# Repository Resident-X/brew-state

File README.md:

# `brew-state` — a model-based controller for a dual-thermoblock espresso machine

Replacing the factory control board in a Sunbeam EM7000 with a controller that actually models the machine: state estimation, a forward horizon, flow and pressure profiling, and a hardware safety chain with no firmware anywhere in it.

This repository is **public domain**. Take any of it.

## How this project is built

Requirements first, then code. The `specs/` graph is finished before firmware starts, and this repo is partly an argument that working in that order is faster rather than slower.

That means the graph is the substance here, and anything under `specs/` describes the machine as it is meant to be — not as it currently is.

## Where to start reading

**If you want to know what this machine is meant to do**, read the personas and journeys first. They are written to be read by a person, not parsed by a tool:

- `specs/personas/` — three stakeholders. The **operator** who makes coffee, the **builder** who designs and commissions it, and the **adopter** who found this published and owns a different machine.
- `specs/journeys/` — what actually happens: pulling a shot, steaming a jug, serving a group, commissioning the plant, correcting drift, keeping the machine in condition.

**If you want to know what constrains it**, read `specs/obligations/`. These are the cross-cutting commitments — electrical and thermal safety, real-time discipline, control-design discipline, verification discipline, open-source maintainability, physical configuration control. The safety obligation is the only one whose authority is external to this project, and it outranks everything else in the graph.

**If you want the detail**, `specs/requirements/` holds the functional and constraint requirements, `specs/definitions/` the vocabulary, and `specs/decisions/` the choices that have been made and why — including the options that were rejected.

**If you are rebuilding this on your own machine**, read [`docs/sunbeam-em7000/reference-machine.md`](docs/sunbeam-em7000/reference-machine.md) first. Everything specific to *our* machine — supply voltage, mains frequency, element ratings, protection trip points — lives in that one file. The requirement graph is written without those values so that replacing that file is the whole job.

## Two different promises

Be clear about which of these you are:

- **Same architecture** (a dual-thermoblock machine): the graph should apply to you, and adapting it should mean supplying your own parameters rather than changing requirements.
- **Different architecture** (single boiler, heat exchanger): the requirements will not all fit — an HX group's temperature depends on time since the last shot, which has no representation in a thermoblock's state at any parameter values. What transfers is the **method**, the tooling and the safety architecture. That is a smaller promise, and it is the honest one.

## Reading the graph

Nodes are `.req.yaml` files — plain YAML with prose in them. Reading needs nothing but a text editor. **Changing them is a different matter, and is covered below.**

**How they connect.** A requirement `derives-from` one or more *criteria* of the node above it, so the chain runs persona → journey → requirement, with each node carrying numbered criteria (`REQ-BREW-TEMP-001.C1`) attached by `criterion-of`. Obligations sit across the top: they are not part of that chain but constrain everything under them, and the safety obligation outranks the lot. Requirements also derive from each other's criteria where one genuinely builds on another. Decisions attach by `addresses`.

**Priorities.** Every requirement carries one:

| | |
|---|---|
| `must` | the system is wrong without it |
| `should` | real value, deliberately ranked below the musts |
| `could` | worth having, and shipping without it is not a defect |

Priority is about whether the system is wrong, not about when something gets built.

## Changing the graph

**Do not hand-edit `.req.yaml` files.** The graph is maintained by [Staircase](#staircase), and the engine is what holds it together: it assigns IDs, places files, wires and validates links, enforces the boundary between the requirement and delivery chains, applies the authoring discipline, and records who changed what and when.

Editing a node by hand bypasses all of that, and the failure mode is quiet. The file still parses. What breaks is underneath — a link pointing at something that no longer exists, a criterion orphaned from its parent, a requirement deriving from a retired one, a change landing with no version behind it and no event recording it. Structural validation does not catch most of that, because nothing is malformed. It is simply wrong, and it stays wrong until something downstream fails for reasons that no longer look connected.

That is the whole reason the engine exists. It is not a formatter over some YAML — it is the thing that knows how a systems and delivery graph has to hold together, so that a person changing one node does not have to.

**A caveat you should know before relying on this.** The engine is not part of this repository and is not currently something you can obtain. So you can read everything here, and you can build from it, but you cannot presently maintain a fork of the graph the way it is meant to be maintained. That is a real limit on what this repo currently offers, and it is tracked in the graph itself rather than hidden — `REQ-PUBLISHED-BUILD-PATH-001` requires every tool the path depends on to be obtainable by someone who is not the author, and that criterion is not met today.

## Staircase

This project is built with Staircase, whose thesis is that disciplined, requirement-driven, complete-the-first-time engineering produces better software, faster, that stays maintainable. This repo is partly a test of that claim in public, on a real physical thing that can burn someone.

One discipline is worth knowing about while reading: **requirements state properties, not mechanisms.** You will not find part numbers, sensor technologies, interface choices or tuning constants in `specs/`. Those are decisions and they live separately. That is also what makes the graph portable to a machine on a different continent running on a different voltage — a requirement that names a mechanism does not travel.

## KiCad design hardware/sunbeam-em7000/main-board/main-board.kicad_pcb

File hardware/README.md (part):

# Hardware

Board designs and the check every one of them has to pass before it is ordered.

- `hardware/<machine>/` holds one machine's board designs, one KiCad project per board in its own folder, and the `separation-basis.yaml`, `pin-allocation.yaml`, `controller-part.yaml`, `parts-specification.yaml`, `catalogue-extract.yaml` and `board-rules.yaml` they are held to, and the `derating-policy.yaml` and `pin-limits.yaml` they are held to where a design's folders hold them.
- `hardware/tools/` holds the pre-order check, the locked-copper check used around routing, the command that renders a board's layout review views, the command that renders a placed board's placement view and measures it, the command that seeds the layout review's proof design, the review kit (the command that runs a declared judged review as forks of one shared context), the layout review's caller for it, the command that writes a committed board's review folder, the critical-routing check's caller and the catalogue helpers it shares with the layout caller, the production-files check's caller and the command that writes a real order's review folder, the schematic review's caller, the command that writes a committed schematic's review folder and the command that proves the fanned-out schematic review (with the proof harness it shares with the layout review's), the command that proves the fanned-out layout review, the commands that convert and draw a board's production files and the command that seeds the proof design's production files, and their tests. They work for any machine.
- `hardware/proof/` holds designs committed only to prove the board tooling and the layout review: `gate-proof` for the pre-order check's rules, `record-keys-proof` for the keys its records carry, `review-proof` for the layout review and the ordering step's production-files check, and `circuit-review-proof` for the schematic review. They are never ordered.

A **board design** is a KiCad project file (`.kicad_pro`) together with the schematic (`.kicad_sch`) and layout (`.kicad_pcb`) of the same name beside it. The check finds every design git tracks, wherever it sits. The layout above is a convention for readers, not something the check depends on. A design is checked once git tracks it: `git add` is enough for the design's own files. The check reads a design only as the repository holds it. KiCad is given a copy of the tracked files alone, each in its place in the repository: everything in the design's folder, every sheet its schematic reaches, and every library its `sym-lib-table` and `fp-lib-table` name, wherever in the repository they sit. A library, sheet or rules file left uncommitted is therefore not used. A sheet the schematic names, a custom rules file or library table beside the project, or a library a table names, that git does not track fails the design by name. So does a library the repository cannot hold at all: one named by an absolute path, one outside the repository, or one reached through a path variable other than `${KIPRJMOD}` and those naming the libraries KiCad installs with itself (`${KICAD10_SYMBOL_DIR}`, `${KICAD10_FOOTPRINT_DIR}` and the like). Name a library from its table as `${KIPRJMOD}/` followed by its path from the design's folder. The separation basis record has to be committed exactly as it stands (see below).

KiCad is run with a configuration the check makes for the run, not the one on the machine running it. That configuration names only the libraries KiCad installs with itself, and no `KICAD…` variable from the environment reaches KiCad. A symbol or footprint whose library only one machine's own KiCad setup names, in its global library tables or its path variables, is therefore reported by KiCad as a library its configuration does not include, and fails the design under `design_library`. Put such a library in the repository and name it in the design's own table.

One KiCad run may take at most 7200 s. The limit is the constant `KICAD_TIMEOUT_S` in `hardware/tools/board_check.py`, and `hardware/tools/board_views.py` reads the same constant, so neither tool has a figure of its own. A run that outlives it fails the design as "KiCad did not finish within 7200 s", with the limit in force named, in the check and in the views command; the wait is finite, so a hung run still fails. The figure rests on a measurement made on 2026-10-31 on the main board with its ground and neutral pours and slots: KiCad's creepage test alone took about 10 minutes and the full design check 20 to 30 minutes. 7200 s is about four times the slowest of those, the margin that lets a slower machine or a denser board finish.

## What you need

Every tool is free. The check stops with an error naming any tool that is missing or too old, rather than skipping the checks that need it.

| Tool | Minimum | Where to get it |
|---|---|---|
| KiCad (its `kicad-cli`) | KiCad 10.0 | https://www.kicad.org/download/. This repository's board files are in KiCad 10's format, which older versions cannot open. |
| Python | Python 3.9 | https://www.python.org/downloads/ |
| PyYAML | PyYAML 5.1 | `pip install pyyaml`, or your system's `python3-yaml` package |
| git | git 2.11 | https://git-scm.com/downloads |
| Task | 3 | https://taskfile.dev/installation/ |
| resvg, for the layout review views and for the tooling tests the build round runs | resvg 0.47 | A prebuilt program from https://github.com/linebender/resvg/releases: the v0.47.0 release carries one for each of Windows (`resvg-win64.zip`), macOS and Linux (x86_64), and later releases carry them for macOS and Linux only. Or `brew install resvg` with Homebrew, on macOS or Linux. Or `cargo install resvg` with a Rust toolchain from https://rustup.rs/, on any operating system. It turns the views into images. The pre-order check itself does not need it, but the tooling tests that the build round and the nightly run draw views, so those need it too ([When the board check runs](#when-the-board-check-runs)). |
| gerbonara, for the commands that draw a board's exported fabrication layers and for the tooling tests the build round runs | gerbonara 1.6.3, exactly | A Python library under the Apache licence, https://pypi.org/project/gerbonara/. Install it into a virtual environment of its own with `task hw:gerbonara`, which makes one in your user cache folder (`GERBONARA_VENV` puts it elsewhere), or by hand with `python3 -m venv <folder>` then `<folder>/bin/python -m pip install gerbonara==1.6.3` (on Windows `<folder>\Scripts\python.exe`) and name that environment's Python as `GERBONARA_PYTHON`. It reads the Gerber and drill files KiCad exports, which `kicad-cli` cannot, and the ordering step of the method turns each into a vector image that resvg rasterises. The pre-order check itself does not need it, but the tooling tests that the build round and the nightly run draw layers from exported files, so those need it too. A command or a test that needs it and does not find that version stops with `CANNOT RUN` naming it. |
| A monospaced font for the captions, for the layout review views and for the tooling tests the build round runs | DejaVu Sans Mono, or Menlo, Consolas, Liberation Mono or Courier New | The captions are drawn in the first of these that resvg finds among the system's fonts. macOS carries Menlo and Windows carries Consolas. Elsewhere, install DejaVu Sans Mono from https://dejavu-fonts.github.io/ or your system's package of it (for example `fonts-dejavu`). Without one the command, or the tooling tests, stop with `CANNOT RUN`. |

`kicad-cli` is often installed off the search path. The tasks use the variable `KICAD_CLI`, which defaults to the bare name `kicad-cli`. If it is not on your search path, set the variable to the tool's full path, either on the command line (`task hw:verify KICAD_CLI=/path/to/kicad-cli`) or in the environment. Its usual location:

| System | `kicad-cli` |
|---|---|
| macOS | `/Applications/KiCad/KiCad.app/Contents/MacOS/kicad-cli` |
| Windows | `C:\Program Files\KiCad\10.0\bin\kicad-cli.exe` |
| Linux (distribution or PPA package) | `/usr/bin/kicad-cli` |
| Linux (Flatpak) | not a file on the path: write a one-line script that runs `flatpak run --command=kicad-cli org.kicad.KiCad "$@"` and point `KICAD_CLI` at it |

`GERBONARA_PYTHON` is the Python of the virtual environment above. The tasks that draw layers use the variable, which defaults to the Python of the environment `task hw:gerbonara` makes and to `python3` when there is none, so only an environment made by hand needs it set, on the command line (`task hw:production-seed GERBONARA_PYTHON=/path/to/venv/bin/python -- ...`) or in the environment.

`resvg` is one program, wherever it was unpacked. The view tasks use the variable `RESVG`, which defaults to the bare name `resvg`. If it is not on your search path, set it to the program's full path, for example `task hw:views RESVG=/path/to/resvg -- ...`.

## The commands

- `task hw:verify` runs the pre-order check on every board design in the repository. It exits 0 only when every design passes. A build round runs it for a change that can matter to a board, and the nightly run of `main` runs it every night ([When the board check runs](#when-the-board-check-runs)).
- `task hw:prove` seeds each fault the check guards against into a throwaway copy of `hardware/proof/gate-proof` (or, for a fault about the keys of a record, of `hardware/proof/record-keys-proof`, for a fault about an unlisted pin of `hardware/proof/circuit-review-proof`, and for a fault about sensing clearance or ground returns of `hardware/proof/review-proof`) as the last commit holds it, in a temporary directory outside the repository, so an uncommitted edit to the proof design is not what it proves. It requires the check to catch each fault. This command is on demand: neither the build round nor the nightly runs it.
- `task hw:review-seed -- --seeds <file> --out <folder>` seeds known layout defects into a throwaway copy of `hardware/proof/review-proof` and writes a folder to review it blind, with the seed list apart (see [The proof designs](#the-proof-designs)). This command is on demand and is not part of the gate. It needs the same tools as `hw:views`.
- `task hw:production-review-folder -- --repo <repository> --commit <commit> --design <board folder> --out <folder> --work <folder> --views <folder> --placement <folder> --preview <folder> --preview-note <text> --tools <text> --command <text> ...` writes the review folder of a real order's production-files check for a judged review to read ([The production-files check by unit](#the-production-files-check-by-unit)). This command is on demand and is not part of the gate. It needs git and Python, no KiCad and no gerbonara.
- `task hw:production-seed -- --seeds <file> --out <folder>` seeds known defects into the production files of `hardware/proof/review-proof` and writes a folder to check them blind, with the seed list apart (see [The proof designs](#the-proof-designs)). This command is on demand and is not part of the gate. It needs the same tools as `hw:views`, and gerbonara.
- `task hw:test` runs the tests of the check itself, of the locked-copper check's four commands, of the layout review views, of the placement view, of the placement and critical routing history check, of the layout review record history check, of the layout review proof's seeding command, of the schematic sheet drawing command, of the review kit (its session specification and executors, answer reading, stream checks and telemetry, declaration, catalogue and shared context, planner and scheduler, merge and replicas, caller contract, contract smoke, the command and the task runner's file), of the layout review's caller, the critical-routing check's caller and the shared catalogue helpers, the production-files check's caller and its folder command, the schematic review's caller, the schematic review folder command and the schematic review proof command, the review folder command, the layout review proof command, the critical-routing review proof command and the production-files review proof command, and of the production-files conversion, rendering and seeding commands, against the real `kicad-cli`, `resvg` and gerbonara. It includes the tests that run the seeded-fault proof, so it is the whole suite, on demand.
- `task hw:test:round` runs the same tests without those that need the seeded-fault proof. It is the tooling-test part of the build round's board tier and of the nightly run ([When the board check runs](#when-the-board-check-runs)). It needs the same tools as `hw:test`: KiCad, resvg, a monospaced font and gerbonara.
  Both tasks run each test file in a process of its own, side by side, through `firmware/tools/run_tool_tests.py` (the runner the firmware tooling's tests use), from the repository root as a serial discovery run does. The runner fails when it finds no test file, names every file that fails, and writes a missing tool's `CANNOT RUN |` line once to its error output so the round reads it as a failure to look. The stage runs at most four files at once unless asked for more (`task hw:test -- --workers 10`), because the machine running the round is shared with other sessions; `task hw:test -- --workers 1` runs the files one after another. The long test files are divided by topic so no one file holds the stage: the KiCad check's tests into `test_board_check_kicad_*.py` (their shared setup and the exclusion of the seeded-fault proof in `board_kicad_fixtures.py`), the layout review views' into `test_board_views_*.py`, the history check's into `test_board_history_*.py`, the locked-copper check's into `test_locked_copper_*.py` and the review proof design's rules into `test_review_proof_rules_*.py`, each with its shared setup in a `*_fixtures.py` beside them; `test_board_kicad_division.py` holds each division to the tests the undivided file held, each in exactly one file. A test class whose tests only read a copy of a proof design and the result of checking it derives from `SharedCopy` and makes the copy and the check once, with the copy fingerprinted and verified unchanged after each test; a test that changes its copy derives from `Copy` and has one of its own.
- `task hw:reads` lists, one per line, every file the board designs git tracks read: each design's folder (with a trailing slash), its sheets, its libraries and the separation basis, pin allocation, controller part, parts specification, catalogue extract, derating policy, pin-limit, board rules and manufacturer limits records it is held to. It runs no check and needs only git and Python, no KiCad. The build round asks it which changed paths reach a board design.
- `task hw:review-run -- --caller <name> --review <folder> --out <folder>` runs a declared judged review as forks of one shared context ([The review kit command](#the-review-kit-command)). This command is on demand: neither the build round nor the nightly runs it. It needs the agent command line on the search path and logged in, and no KiCad.
- `task hw:review-smoke -- --out <folder>` runs the review kit's contract smoke, seven small probes of the installed agent command line for a few cents ([The review kit command](#the-review-kit-command)). This command is on demand: neither the build round nor the nightly runs it. It needs the agent command line on the search path and logged in, and no KiCad.
- `task hw:review-folder -- --repo <repository> --commit <commit> --design <board folder> --out <folder> ...` writes the review folder of a committed board for a judged review to read (with `--review critical-routing`, the critical-routing check's), and adds a rendered view or a text file to one it wrote ([The layout review by unit](#the-layout-review-by-unit), [The critical-routing check by unit](#the-critical-routing-check-by-unit)). This command is on demand and is not part of the gate. It needs git and Python and no KiCad.
- `task hw:review-proof -- --work <folder>` proves the fanned-out layout review on one seeded copy of `hardware/proof/review-proof` against the recorded single-reviewer runs, in one command ([The layout review by unit](#the-layout-review-by-unit)); with `--dry` it prints the plan and the predicted cost and time and starts no session. This command is on demand, spends the agent command line's usage and is not part of the gate. It needs the agent command line on the search path and logged in, and the same tools as `hw:review-seed`.
- `task hw:schematic-review-folder -- --repo <repository> --commit <commit> --design <board folder> --out <folder> --netlist <file> --netlist-command <text> --sheets <folder> --check-report <file> --number <n> --record <file> ...` writes the review folder of a committed schematic for the schematic review to read, and adds a sheet drawing, a view or a text file to one it wrote ([The schematic review by unit](#the-schematic-review-by-unit)). This command is on demand and is not part of the gate. It needs git and Python and no KiCad.
- `task hw:schematic-review-proof -- --work <folder> --seeded-repo <work tree> --seeds <file>` proves the fanned-out schematic review on one seeded copy of `hardware/proof/circuit-review-proof` against its single-reviewer run, in one command ([The schematic review by unit](#the-schematic-review-by-unit)); with `--dry` it prints the plan and the predicted cost and time and starts no session. This command is on demand, spends the agent command line's usage and is not part of the gate. It needs the agent command line on the search path and logged in, KiCad 10.0 or newer, and the seeding session's work tree and seed list.
- `task hw:critical-routing-review-proof -- --work <folder> --seeded-repo <work tree> --seeds <file>` proves the fanned-out critical-routing check on one seeded copy of `hardware/proof/method-proof` against its single-reviewer run, in one command ([The critical-routing check by unit](#the-critical-routing-check-by-unit)); with `--dry` it prints the plan and the predicted cost and time and starts no session. This command is on demand, spends the agent command line's usage and is not part of the gate. It needs the agent command line on the search path and logged in, the same tools as `hw:views`, and the seeding session's work tree and seed list.
- `task hw:production-files-review-proof -- --work <folder> --folder <production-files folder> --seeds <file>` proves the fanned-out production-files check on the seeded production files `task hw:production-seed` writes against its single-reviewer run, in one command ([The production-files check by unit](#the-production-files-check-by-unit)); with `--dry` it prints the plan and the predicted cost and time and starts no session. This command is on demand, spends the agent command line's usage and is not part of the gate. It needs the agent command line on the search path and logged in, and nothing else of its own: the folder and the seed list come from `hw:production-seed`.
- `task hw:views` renders every view the layout review judges one board on (below). It needs the same tools as `hw:verify`, and resvg.
- `task hw:placement` renders one placed board's placement view and writes its measures (below). It needs the same tools as `hw:views`.
- `task hw:sheets -- --out <folder>` draws every sheet of every board design git tracks, one image file for each sheet ([The schematic sheets](#the-schematic-sheets)). It needs KiCad and nothing else.
- `task hw:history` judges one board's placement and critical routing sections of its `layout-plan.md` against the repository's history (below). It needs git and Python only.
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
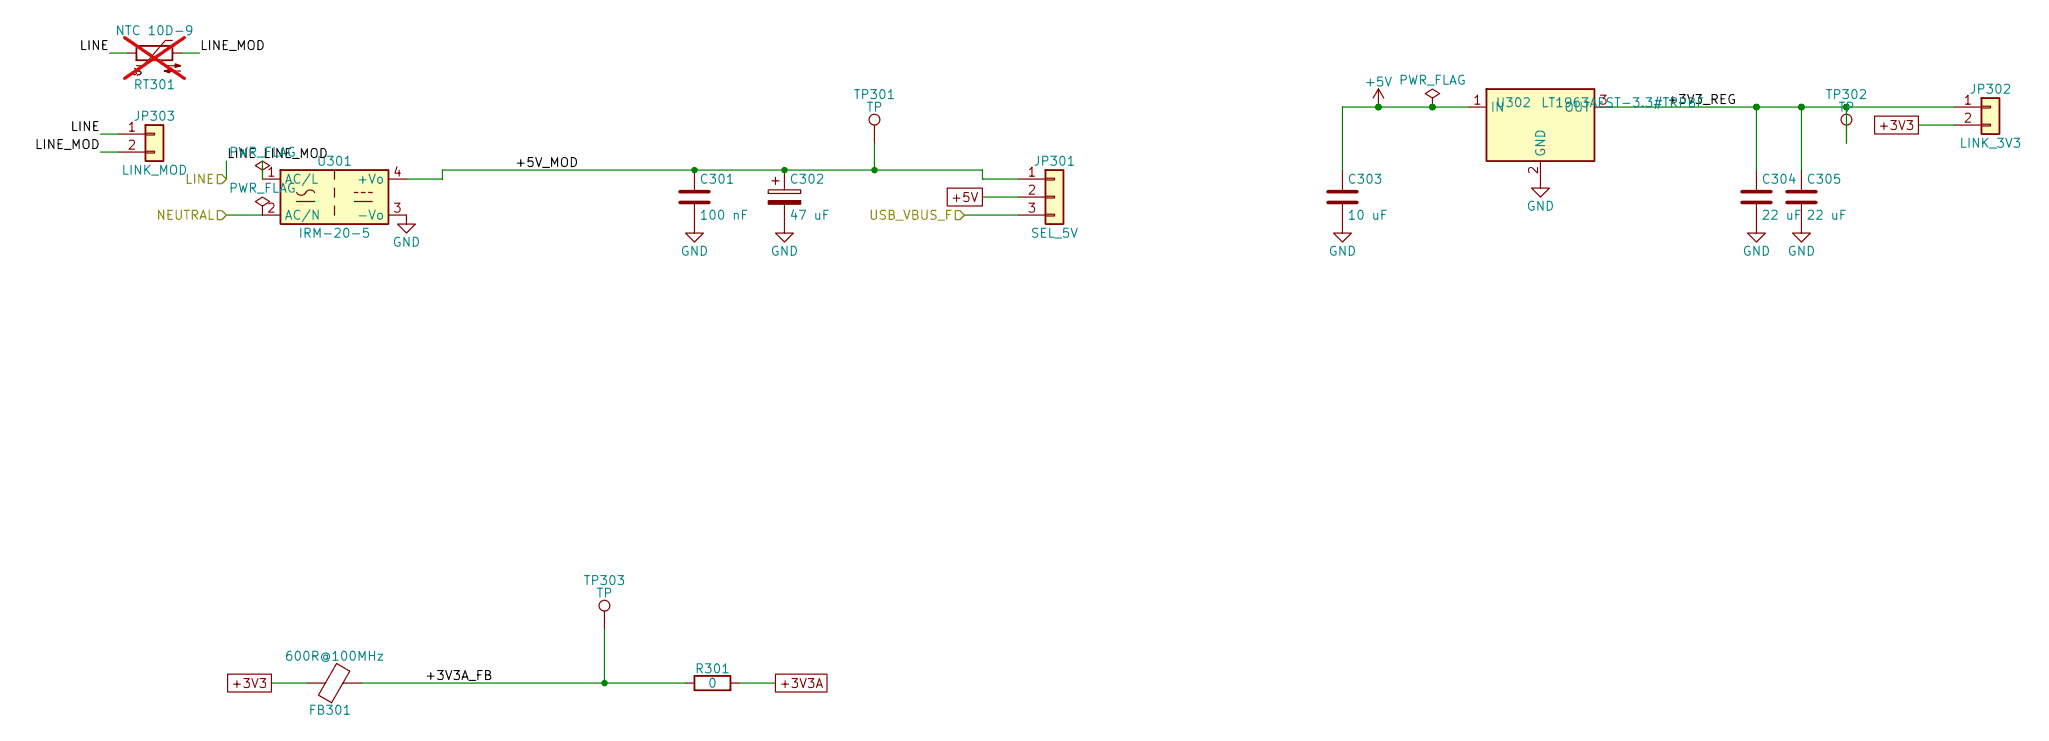
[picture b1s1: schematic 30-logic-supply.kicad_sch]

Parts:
C301: 100 nF; C_0603_1608Metric; Rating X7R 50 V 10 % 0603; MPN CC0603KRX7R9BB104; LCSC C14663
C302: 47 uF; CP_Elec_6.3x5.2; Rating aluminium electrolytic 16 V 20 % SMD 6.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; MPN MVK 16V47 M 6.3*5.2; LCSC C165623
C303: 10 uF; C_0603_1608Metric; Rating X5R 10 V 10 % 0603; MPN CL10A106KP8NNNC; LCSC C19702
C304, C305: 22 uF; C_0805_2012Metric; Rating X5R 10 V 20 % 0805, 85 degC; MPN LMK212BBJ226MG-T; LCSC C92811
FB301: 600R@100MHz; L_0603_1608Metric; Rating 0603, 0.50 ohm DC max, 350 mA, 25 %; MPN FCM1608KF-601T03; LCSC C141723
JP301: SEL_5V; PinHeader_1x03_P2.54mm_Vertical; Rating 1x3 2.54 mm header with one shorting ju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; MPN PZ254V-11-03P; LCSC C2937625
JP302: LINK_3V3; PinHeader_1x02_P2.54mm_Vertical; Rating 1x2 2.54 mm header with shorting jumper; MPN PZ254V-11-02P; LCSC C492401
JP303: LINK_MOD; JP101_WireLink_P10mm; Rating two plated holes for a wire link (1.5 m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; MPN none (owner-fitted wire); LCSC none
R301: 0; R_0603_1608Metric; Rating 0 ohm 0603 100 mW; MPN 0603WAF0000T5E; LCSC C21189
RT301: NTC 10D-9; C_Disc_D11.0mm_W5.0mm_P7.50mm; Rating NTC inrush limiter 10 ohm at 25 degC +/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; MPN NTC 10D-9; LCSC C3790; not fitted
TP301, TP302, TP303: TP; TestPoint_Pad_D1.5mm; Rating pad 1.5 mm; LCSC none
U301: IRM-20-5; Converter_ACDC_MeanWell_IRM-20-xx_THT; Rating 85-305 Vac input, 5 V 4 A, 4.2 kVac in-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; MPN IRM-20-5; LCSC C6280121
U302: LT1963AEST-3.3#TRPBF; SOT-223-3_TabPin2; Rating input and output pins +/-20 V absolute 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; MPN LT1963AEST-3.3#TRPBF; LCSC C459918

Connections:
/LINE: JP303.1, RT301.1; also elsewhere on the board
/Logic supply/+3V3A_FB: FB301.2, R301.1, TP303.1 (1_1)
/Logic supply/+3V3_REG: C304.1, C305.1, JP302.1, TP302.1 (1_1), U302.3 (OUT)
/Logic supply/+5V_MOD: C301.1, C302.1, JP301.1, TP301.1 (1_1), U301.4 (+Vo)
/USB_VBUS_F: JP301.3; also elsewhere on the board
GND: C301.2, C302.2, C303.2, C304.2, C305.2, U301.3 (-Vo), U302.2 (GND); also elsewhere on the board

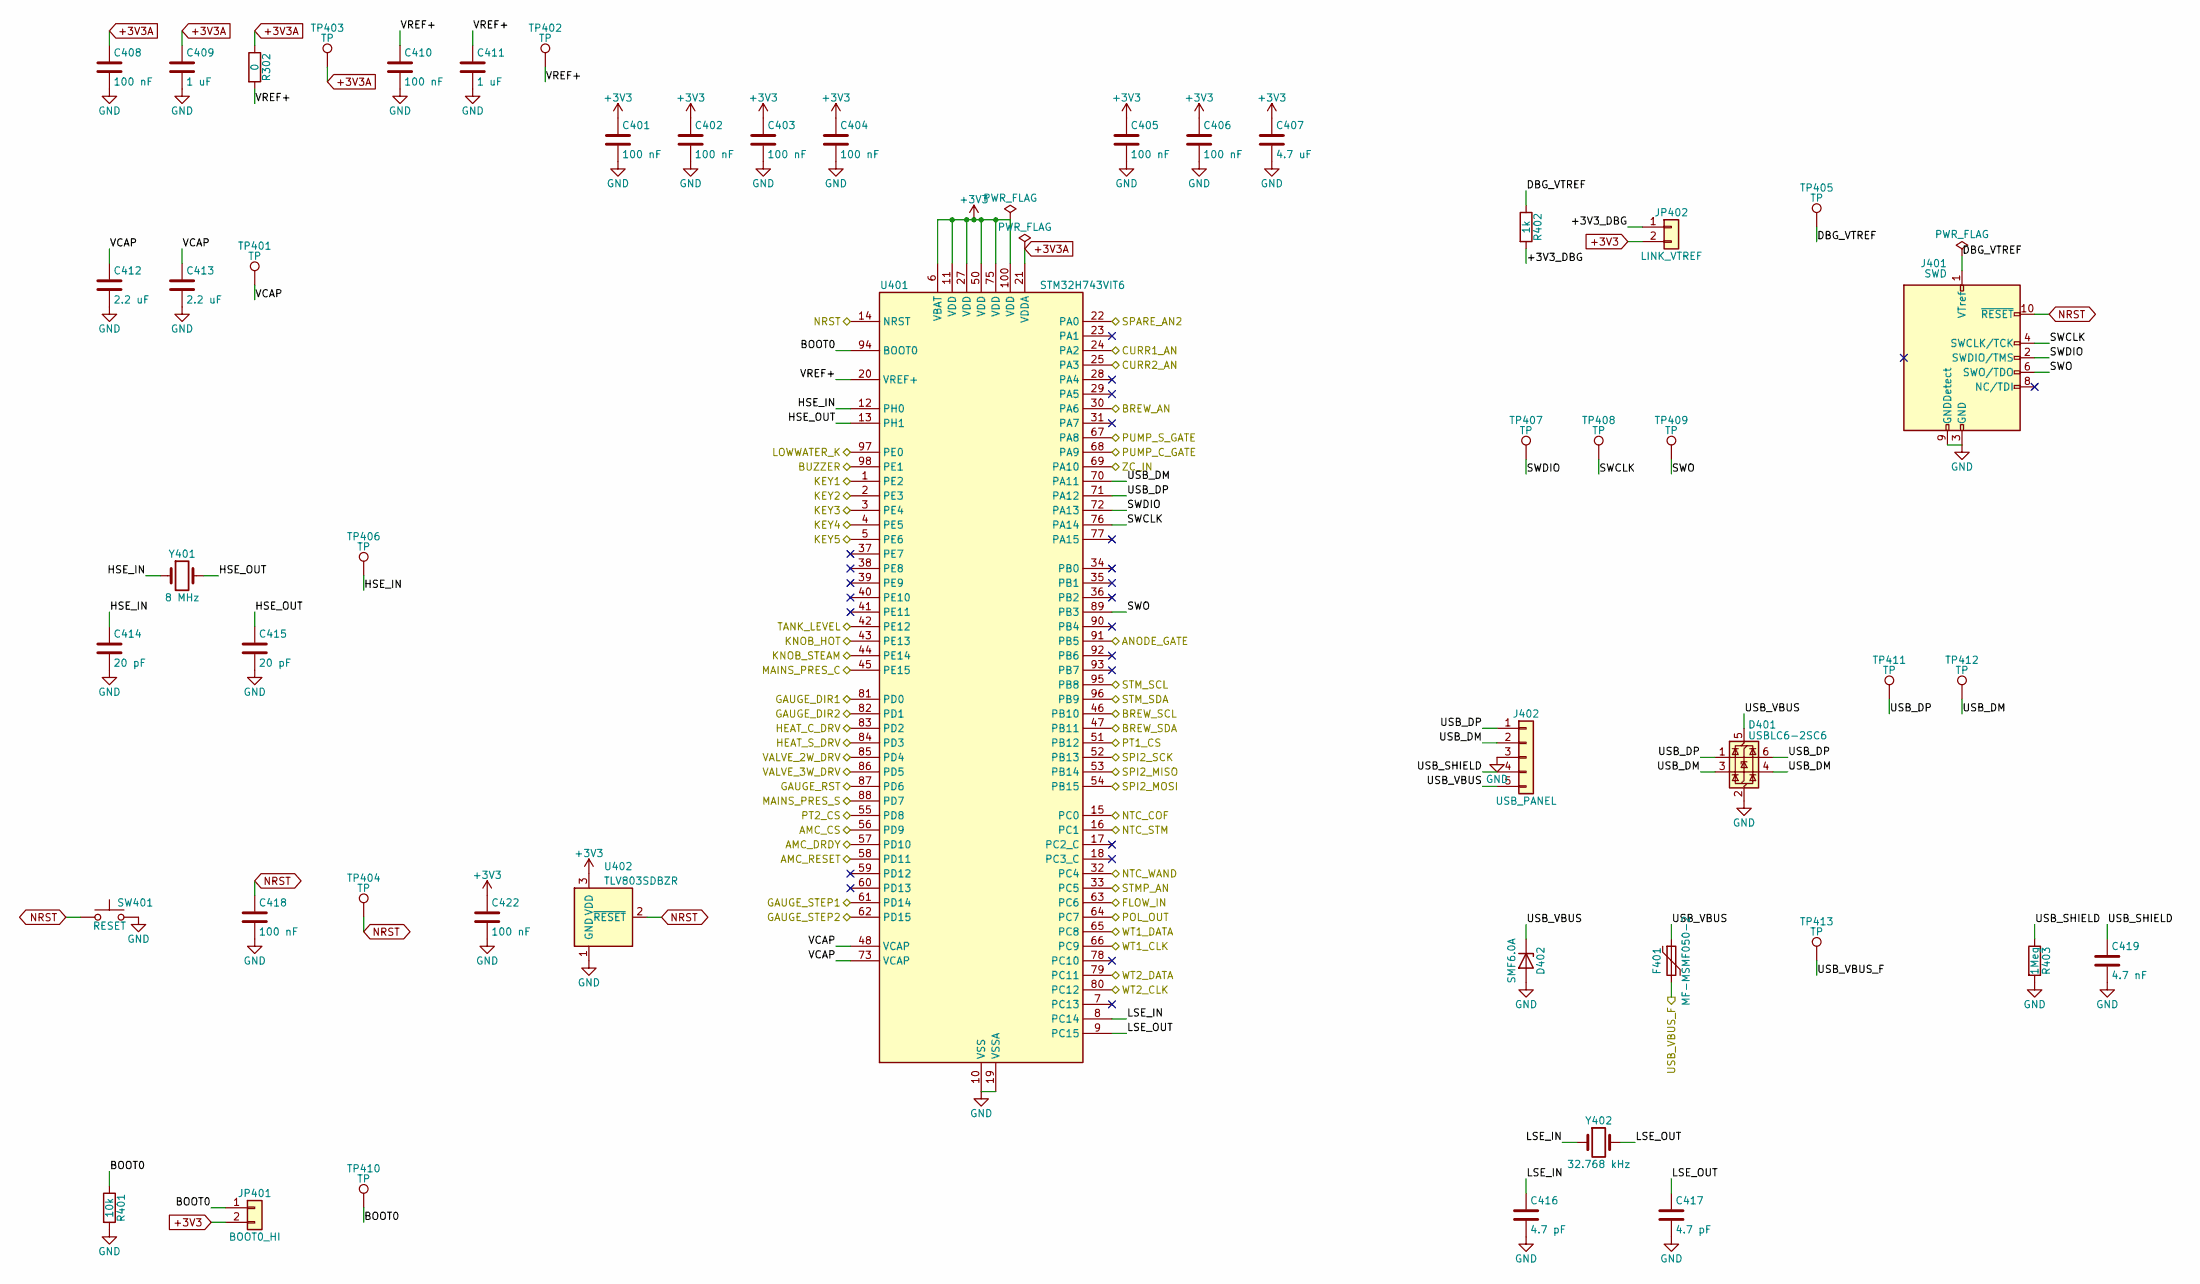
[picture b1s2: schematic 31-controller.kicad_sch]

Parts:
C401, C402, C403, C404, C405, C406, C408, C410, C418, C422: 100 nF; C_0603_1608Metric; Rating X7R 50 V 10 % 0603; MPN CC0603KRX7R9BB104; LCSC C14663
C407: 4.7 uF; C_0603_1608Metric; Rating X5R 16 V 10 % 0603; MPN CL10A475KO8NNNC; LCSC C19666
C409, C411: 1 uF; C_0603_1608Metric; Rating X5R 50 V 10 % 0603; MPN CL10A105KB8NNNC; LCSC C15849
C412, C413: 2.2 uF; C_0603_1608Metric; Rating X5R 16 V 10 % 0603; MPN CL10A225KO8NNNC; LCSC C23630
C414, C415: 20 pF; C_0603_1608Metric; Rating C0G 50 V 5 % 0603; MPN CL10C200JB8NNNC; LCSC C1648
C416, C417: 4.7 pF; C_0603_1608Metric; Rating C0G 50 V 0.25 pF 0603; MPN 0603CG4R7C500NT; LCSC C1669
C419: 4.7 nF; C_1206_3216Metric; Rating X7R 1000 V 10 % 1206; MPN CC1206KKX7RCBB472; LCSC C107198
D401: USBLC6-2SC6; SOT-23-6; Rating 5.25 V reverse stand-off, 2-line ESD ar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; MPN USBLC6-2SC6; LCSC C7519
D402: SMF6.0A; D_SOD-123F; Rating unidirectional TVS 200 W, VR 6.0 V, VBR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; MPN SMF6.0A; LCSC C207260
F401: MF-MSMF050-2; Fuse_1812_4532Metric; Rating PTC 0.50 A hold, 1.00 A trip, 15 V, 100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; MPN MF-MSMF050-2; LCSC C17313
J401: SWD; PinHeader_2x05_P1.27mm_Vertical_SMD; Rating 2x5 1.27 mm SMD pin header, Cortex Debu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; MPN PZ1.27-2x5P TP; LCSC C41376037
J402: USB_PANEL; PinHeader_1x05_P2.54mm_Vertical; Rating 1x5 2.54 mm header; carries D+, D-, GND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; MPN PZ254V-11-05P; LCSC C492404
JP401: BOOT0_HI; PinHeader_1x02_P2.54mm_Vertical; Rating 1x2 2.54 mm header with shorting jumper; MPN PZ254V-11-02P; LCSC C492401
JP402: LINK_VTREF; PinHeader_1x02_P2.54mm_Vertical; Rating 1x2 2.54 mm header with shorting jumper; MPN PZ254V-11-02P; LCSC C492401
R302: 0; R_0603_1608Metric; Rating 0 ohm 0603 100 mW; MPN 0603WAF0000T5E; LCSC C21189
R401: 10k; R_0603_1608Metric; Rating 1 % 0603 100 mW; MPN 0603WAF1002T5E; LCSC C25804
R402: 1k; R_0603_1608Metric; Rating 1 % 0603 100 mW; MPN 0603WAF1001T5E; LCSC C21190
R403: 1Meg; R_1206_3216Metric; Rating 1 % 1206 250 mW, 200 V max working; MPN 1206W4F1004T5E; LCSC C17927
SW401: RESET; TS1187A_5.1x5.1mm_SMD; Rating tactile 5.1x5.1 mm, 50 mA 12 V dc, cont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; MPN TS-1187A-B-A-B; LCSC C318884
TP401, TP402, TP403, TP404, TP405, TP406, TP407, TP408, TP409, TP410, TP411, TP412, TP413: TP; TestPoint_Pad_D1.0mm_Tight; Rating pad 1.5 mm; LCSC none
U401: STM32H743VIT6; LQFP-100_14x14mm_P0.5mm; Rating LQFP-100 14x14 mm, 0.5 mm pitch, -40..8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; MPN STM32H743VIT6; LCSC C114409
U402: TLV803SDBZR; SOT-23; Rating 7 V absolute maximum VDD, 3.3 V supervi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; MPN TLV803SDBZR; LCSC C132016
Y401: 8 MHz; Crystal_SMD_5032-2Pin_5.0x3.2mm; Rating YSX530GA 20 pF, +/-10 ppm, ESR 80 ohm m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; MPN X50328MSB2GI; LCSC C115962
Y402: 32.768 kHz; Crystal_SMD_3215-2Pin_3.2x1.5mm; Rating FC-135 12.5 pF, +/-20 ppm, R1 70 kohm m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; MPN Q13FC13500004; LCSC C32346

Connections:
/AMC_CS: U401.56 (PD9); also elsewhere on the board
/AMC_DRDY: U401.57 (PD10); also elsewhere on the board
/AMC_RESET: U401.58 (PD11); also elsewhere on the board
/ANODE_GATE: U401.91 (PB5); also elsewhere on the board
/BREW_AN: U401.30 (PA6); also elsewhere on the board
/BREW_SCL: U401.46 (PB10); also elsewhere on the board
/BREW_SDA: U401.47 (PB11); also elsewhere on the board
/BUZZER: U401.98 (PE1); also elsewhere on the board
/CURR1_AN: U401.24 (PA2); also elsewhere on the board
/CURR2_AN: U401.25 (PA3); also elsewhere on the board
/Controller/+3V3_DBG: JP402.1, R402.2
/Controller/BOOT0: JP401.1, R401.1, TP410.1 (1_1), U401.94 (BOOT0)
/Controller/HSE_IN: C414.1, TP406.1 (1_1), U401.12 (PH0), Y401.1
/Controller/HSE_OUT: C415.1, U401.13 (PH1), Y401.2
/Controller/LSE_IN: C416.1, U401.8 (PC14), Y402.1
/Controller/LSE_OUT: C417.1, U401.9 (PC15), Y402.2
/Controller/SWCLK: J401.4 (SWCLK/TCK), TP408.1 (1_1), U401.76 (PA14)
/Controller/SWDIO: J401.2 (SWDIO/TMS), TP407.1 (1_1), U401.72 (PA13)
/Controller/SWO: J401.6 (SWO/TDO), TP409.1 (1_1), U401.89 (PB3)
/Controller/USB_DM: D401.3 (I/O2), D401.4 (I/O2), J402.2, TP412.1 (1_1), U401.70 (PA11)
/Controller/USB_DP: D401.1 (I/O1), D401.6 (I/O1), J402.1, TP411.1 (1_1), U401.71 (PA12)
/Controller/USB_SHIELD: C419.1, J402.4, R403.1
/Controller/USB_VBUS: D401.5 (VBUS), D402.1 (A1), F401.1, J402.5
/Controller/VCAP: C412.1, C413.1, TP401.1 (1_1), U401.48 (VCAP), U401.73 (VCAP)
/Controller/VREF+: C410.1, C411.1, R302.2, TP402.1 (1_1), U401.20 (VREF+)
/FLOW_IN: U401.63 (PC6); also elsewhere on the board
/GAUGE_DIR1: U401.81 (PD0); also elsewhere on the board
/GAUGE_DIR2: U401.82 (PD1); also elsewhere on the board
/GAUGE_RST: U401.87 (PD6); also elsewhere on the board
/GAUGE_STEP1: U401.61 (PD14); also elsewhere on the board
/GAUGE_STEP2: U401.62 (PD15); also elsewhere on the board
/HEAT_C_DRV: U401.83 (PD2); also elsewhere on the board
/HEAT_S_DRV: U401.84 (PD3); also elsewhere on the board
/KEY1: U401.1 (PE2); also elsewhere on the board
/KEY2: U401.2 (PE3); also elsewhere on the board
/KEY3: U401.3 (PE4); also elsewhere on the board
/KEY4: U401.4 (PE5); also elsewhere on the board
/KEY5: U401.5 (PE6); also elsewhere on the board
/KNOB_HOT: U401.43 (PE13); also elsewhere on the board
/KNOB_STEAM: U401.44 (PE14); also elsewhere on the board
/LOWWATER_K: U401.97 (PE0); also elsewhere on the board
/MAINS_PRES_C: U401.45 (PE15); also elsewhere on the board
/MAINS_PRES_S: U401.88 (PD7); also elsewhere on the board
/NTC_COF: U401.15 (PC0); also elsewhere on the board
/NTC_STM: U401.16 (PC1); also elsewhere on the board
/NTC_WAND: U401.32 (PC4); also elsewhere on the board
/POL_OUT: U401.64 (PC7); also elsewhere on the board
/PT1_CS: U401.51 (PB12); also elsewhere on the board
/PT2_CS: U401.55 (PD8); also elsewhere on the board
/PUMP_C_GATE: U401.68 (PA9); also elsewhere on the board
/PUMP_S_GATE: U401.67 (PA8); also elsewhere on the board
/SPARE_AN2: U401.22 (PA0); also elsewhere on the board
/SPI2_MISO: U401.53 (PB14); also elsewhere on the board
/SPI2_MOSI: U401.54 (PB15); also elsewhere on the board
/SPI2_SCK: U401.52 (PB13); also elsewhere on the board
/STMP_AN: U401.33 (PC5); also elsewhere on the board
/STM_SCL: U401.95 (PB8); also elsewhere on the board
/STM_SDA: U401.96 (PB9); also elsewhere on the board
/TANK_LEVEL: U401.42 (PE12); also elsewhere on the board
/USB_VBUS_F: F401.2, TP413.1 (1_1); also elsewhere on the board
/VALVE_2W_DRV: U401.85 (PD4); also elsewhere on the board
/VALVE_3W_DRV: U401.86 (PD5); also elsewhere on the board
/WT1_CLK: U401.66 (PC9); also elsewhere on the board
/WT1_DATA: U401.65 (PC8); also elsewhere on the board
/WT2_CLK: U401.80 (PC12); also elsewhere on the board
/WT2_DATA: U401.79 (PC11); also elsewhere on the board
/ZC_IN: U401.69 (PA10); also elsewhere on the board
GND: C401.2, C402.2, C403.2, C404.2, C405.2, C406.2, C407.2, C408.2, C409.2, C410.2, C411.2, C412.2, C413.2, C414.2, C415.2, C416.2, C417.2, C418.2, C419.2, C422.2, D401.2 (GND), D402.2 (A2), J401.3 (GND), J401.5 (GND), J401.9 (GNDDetect), J402.3, R401.2, R403.2, SW401.2, U401.10 (VSS), U401.19 (VSSA), U401.26 (VSS), U401.49 (VSS), U401.74 (VSS), U401.99 (VSS), U402.1 (GND); also elsewhere on the board
NRST: C418.1, J401.10 (~RESET), SW401.1, TP404.1 (1_1), U401.14 (NRST), U402.2 (~RESET)

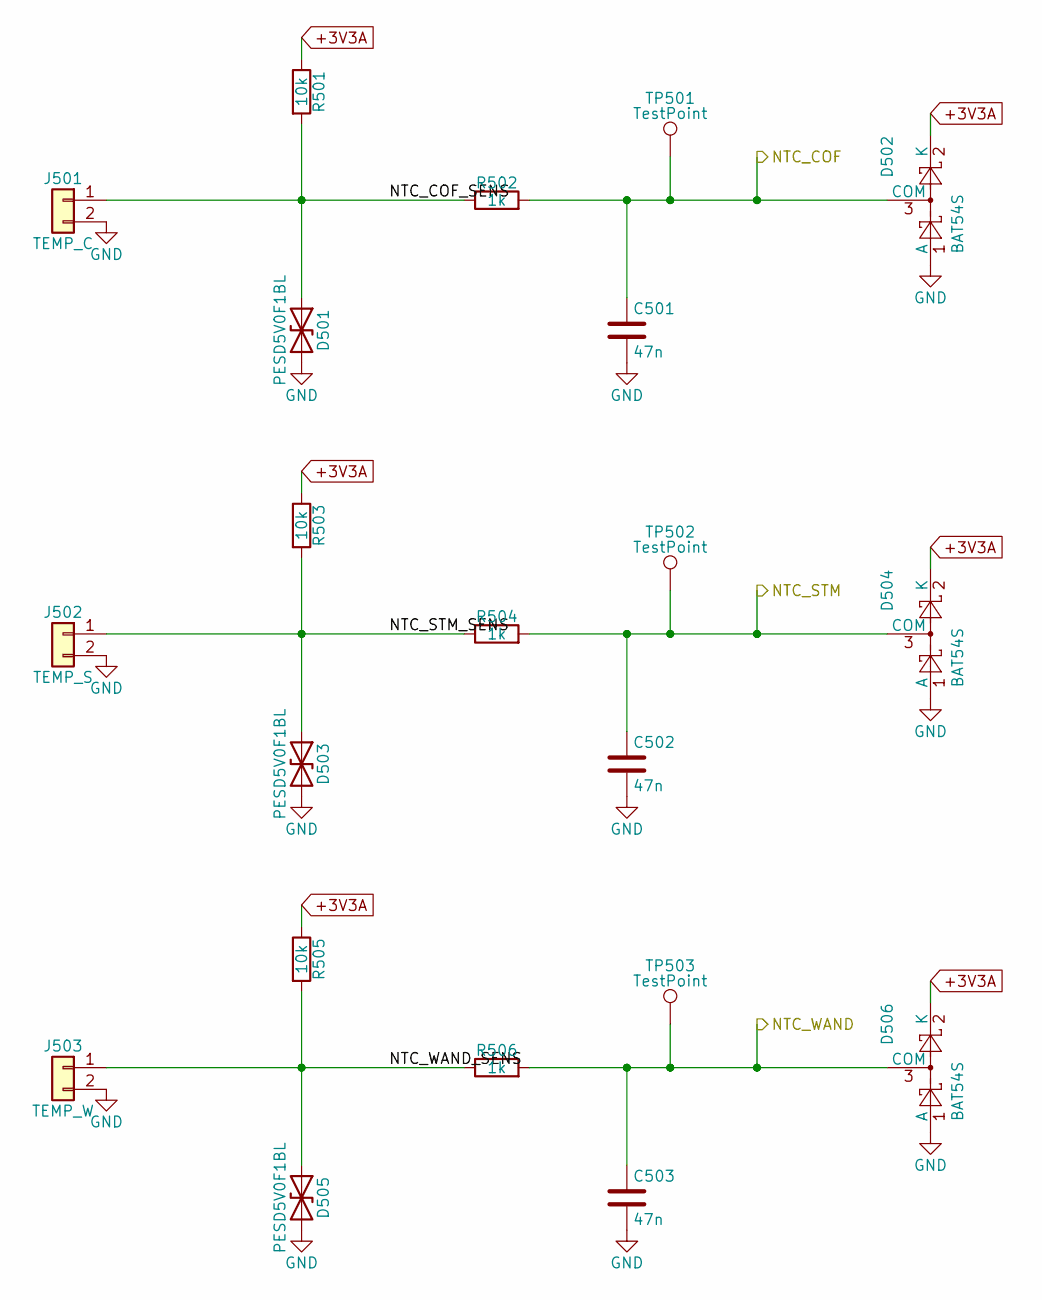
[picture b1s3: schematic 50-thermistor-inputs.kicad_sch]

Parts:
C501, C502, C503: 47n; C_0603_1608Metric; Rating 10% X7R 50V 0603; MPN CL10B473KB8NNNC; LCSC C1622
D501, D503, D505: PESD5V0F1BL; D_SOD-882; Rating bidirectional 5.5V standoff, 0.55pF max; MPN PESD5V0F1BL,315; LCSC C45961
D502, D504, D506: BAT54S; SOT-23; Rating dual series Schottky 30V 200mA; MPN BAT54S,215; LCSC C47546
J501: TEMP_C; PinHeader_1x02_P2.54mm_Vertical; Rating 2.54mm 0.63mm pins; MPN 2.54mm 1x2 header; LCSC C32713268
J502: TEMP_S; PinHeader_1x02_P2.54mm_Vertical; Rating 2.54mm 0.63mm pins; MPN 2.54mm 1x2 header; LCSC C32713268
J503: TEMP_W; PinHeader_1x02_P2.54mm_Vertical; Rating 2.54mm 0.63mm pins; MPN 2.54mm 1x2 header; LCSC C32713268
R501, R503, R505: 10k; R_0603_1608Metric; Rating 1% 100ppm/K 0603 100mW; MPN 0603WAF1002T5E; LCSC C25804
R502, R504, R506: 1k; R_0603_1608Metric; Rating 1% 100ppm/K 0603 100mW; MPN 0603WAF1001T5E; LCSC C21190
TP501, TP502, TP503: TestPoint; TestPoint_Pad_D1.0mm_Tight; Rating pad 1.5mm; LCSC none

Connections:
/NTC_COF: C501.1, D502.3 (COM), R502.2, TP501.1 (1_1); also elsewhere on the board
/NTC_STM: C502.1, D504.3 (COM), R504.2, TP502.1 (1_1); also elsewhere on the board
/NTC_WAND: C503.1, D506.3 (COM), R506.2, TP503.1 (1_1); also elsewhere on the board
/Thermistor inputs/NTC_COF_SENS: D501.1 (A1), J501.1, R501.2, R502.1
/Thermistor inputs/NTC_STM_SENS: D503.1 (A1), J502.1, R503.2, R504.1
/Thermistor inputs/NTC_WAND_SENS: D505.1 (A1), J503.1, R505.2, R506.1
GND: C501.2, C502.2, C503.2, D501.2 (A2), D502.1 (A), D503.2 (A2), D504.1 (A), D505.2 (A2), D506.1 (A), J501.2, J502.2, J503.2; also elsewhere on the board

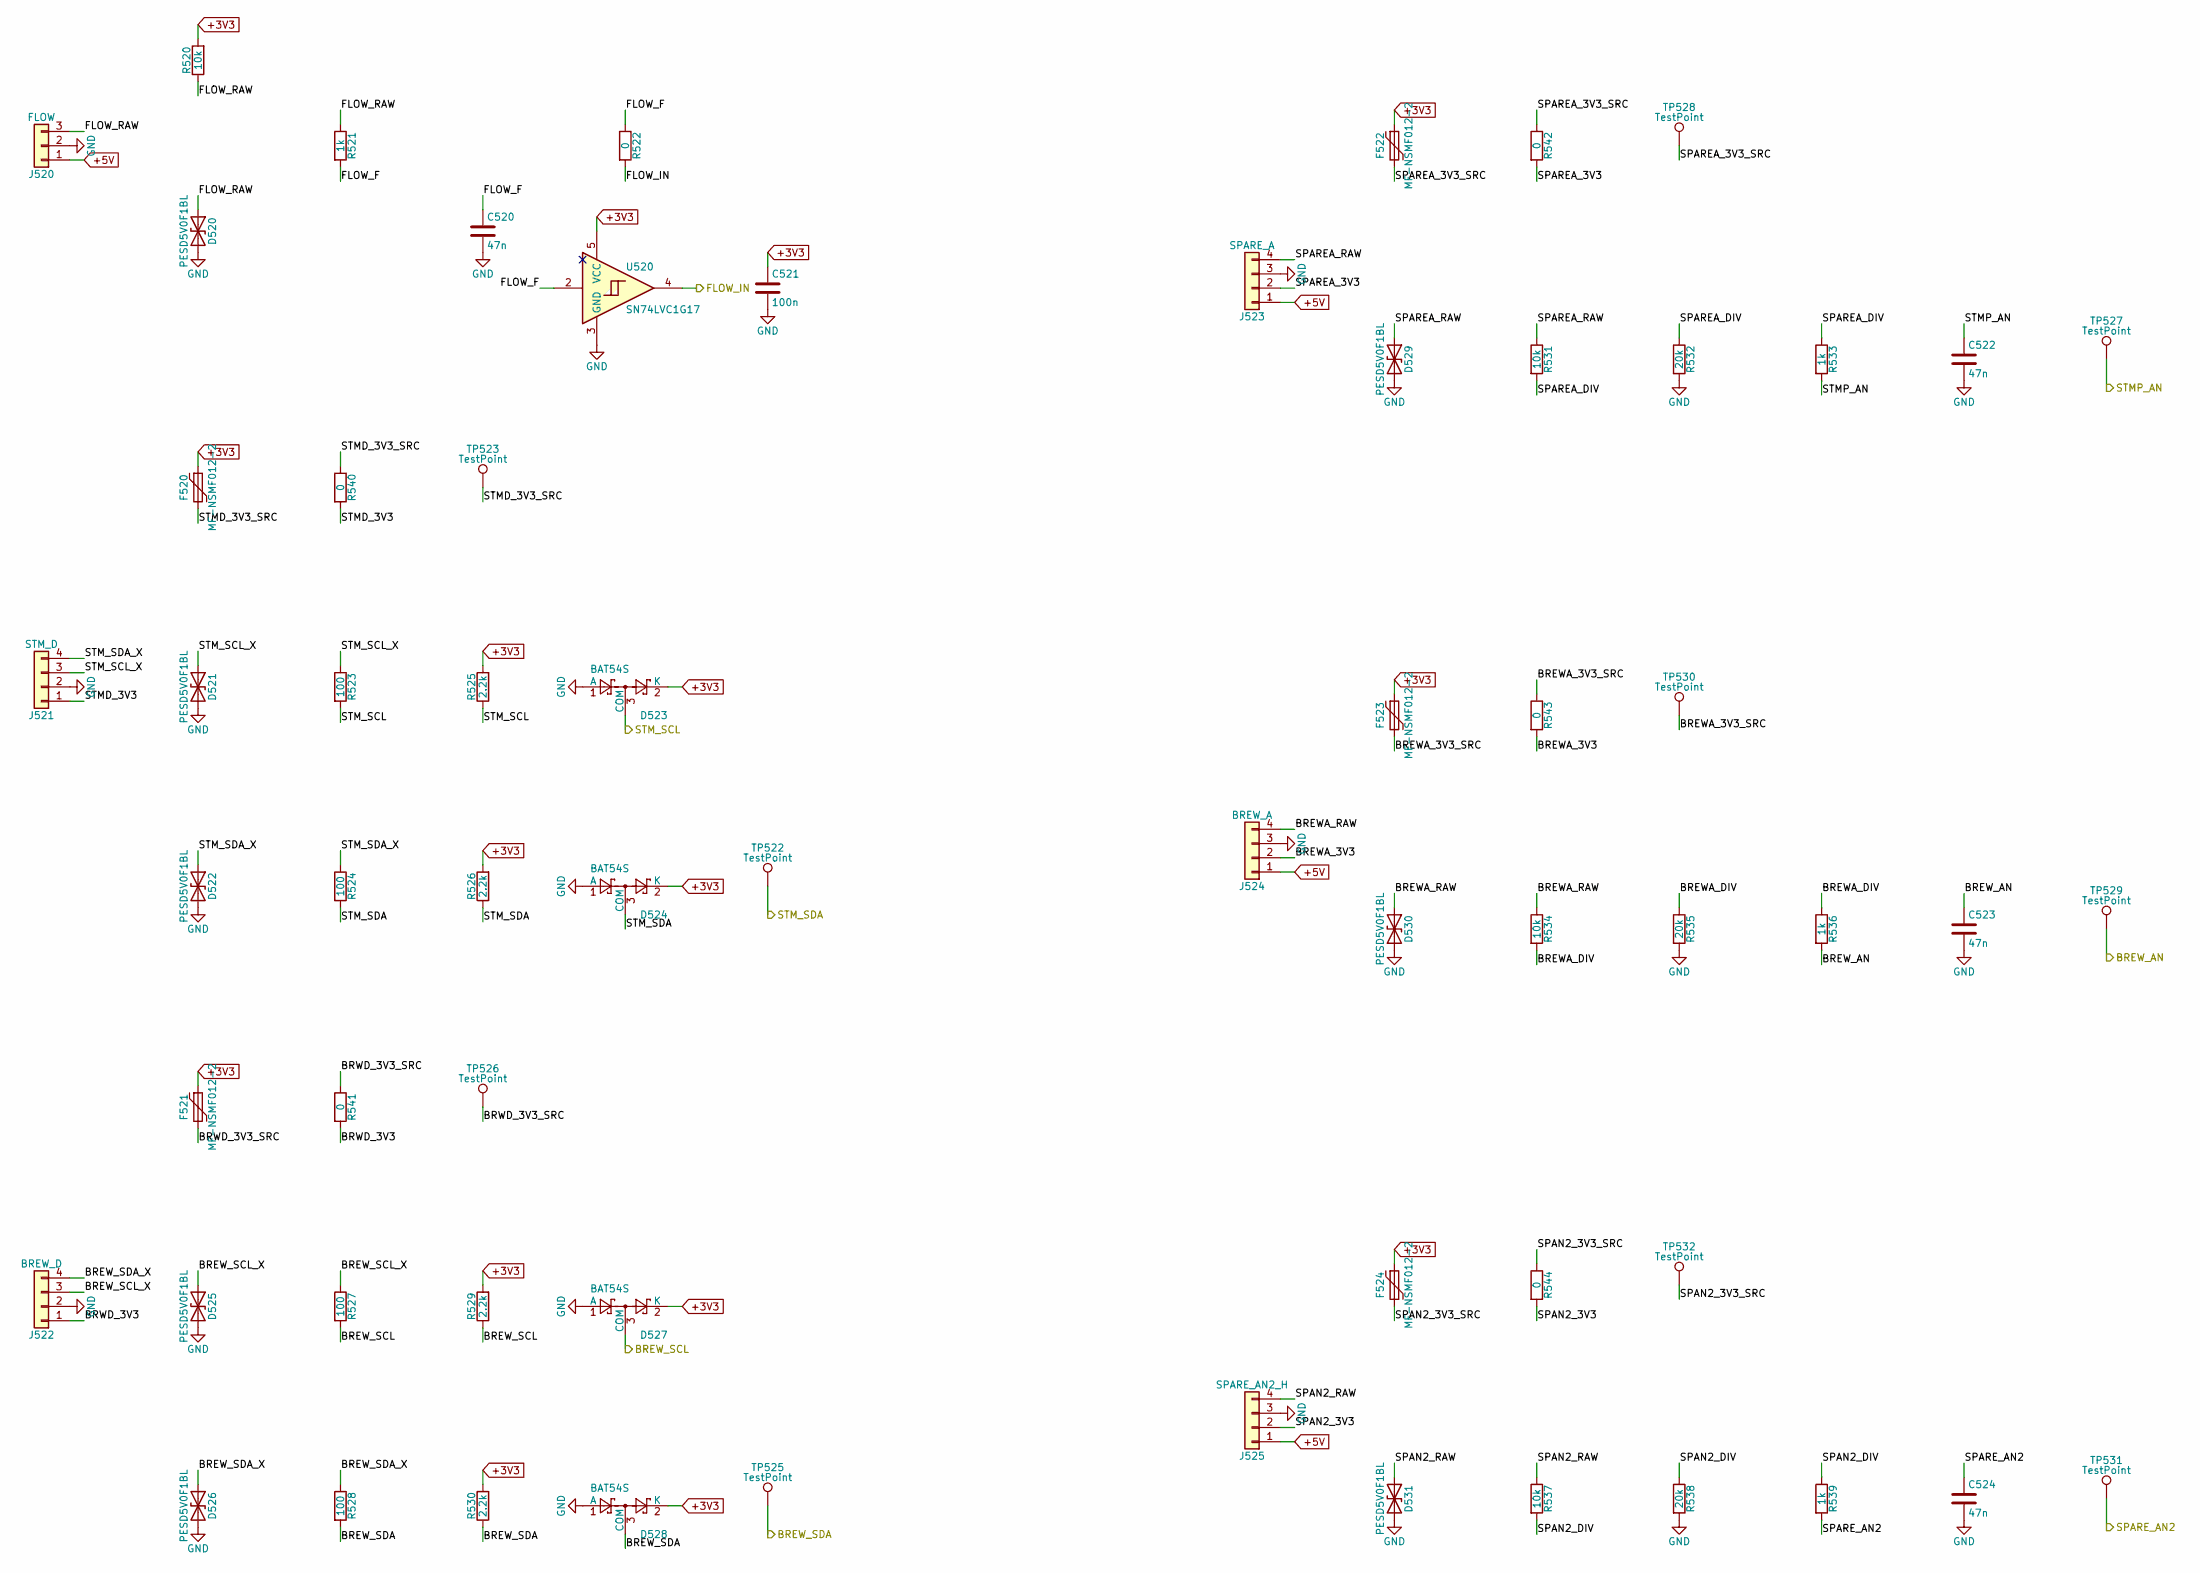
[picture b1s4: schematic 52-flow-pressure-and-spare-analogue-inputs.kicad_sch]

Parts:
C520, C522, C523, C524: 47n; C_0603_1608Metric; Rating 10% X7R 50V 0603; MPN CL10B473KB8NNNC; LCSC C1622
C521: 100n; C_0603_1608Metric; Rating 10% X7R 50V 0603; MPN CC0603KRX7R9BB104; LCSC C14663
D520, D521, D522, D525, D526, D529, D530, D531: PESD5V0F1BL; D_SOD-882; Rating bidirectional 5.5V standoff, 0.55pF max; MPN PESD5V0F1BL,315; LCSC C45961
D523, D524, D527, D528: BAT54S; SOT-23; Rating dual series Schottky 30V 200mA; MPN BAT54S,215; LCSC C47546
F520, F521, F522, F523, F524: MF-NSMF012-2; Fuse_1206_3216Metric; Rating PTC 0.12A hold 0.29A trip 30V; MPN MF-NSMF012-2; LCSC C163517
J520: FLOW; PinHeader_1x03_P2.54mm_Vertical; Rating 2.54mm 0.63mm pins; MPN 2.54mm 1x3 header; LCSC C49257
J521: STM_D; PinHeader_1x04_P2.54mm_Vertical; Rating 2.54mm 0.63mm pins; MPN 2.54mm 1x4 header; LCSC C32713270
J522: BREW_D; PinHeader_1x04_P2.54mm_Vertical; Rating 2.54mm 0.63mm pins; MPN 2.54mm 1x4 header; LCSC C32713270
J523: SPARE_A; PinHeader_1x04_P2.54mm_Vertical; Rating 2.54mm 0.63mm pins; MPN 2.54mm 1x4 header; LCSC C32713270
J524: BREW_A; PinHeader_1x04_P2.54mm_Vertical; Rating 2.54mm 0.63mm pins; MPN 2.54mm 1x4 header; LCSC C32713270
J525: SPARE_AN2_H; PinHeader_1x04_P2.54mm_Vertical; Rating 2.54mm 0.63mm pins; MPN 2.54mm 1x4 header; LCSC C32713270
R520, R531, R534, R537: 10k; R_0603_1608Metric; Rating 1% 100ppm/K 0603 100mW; MPN 0603WAF1002T5E; LCSC C25804
R521, R533, R536, R539: 1k; R_0603_1608Metric; Rating 1% 100ppm/K 0603 100mW; MPN 0603WAF1001T5E; LCSC C21190
R522: 0; R_0603_1608Metric; Rating 0603 zero-ohm link; MPN 0603WAF0000T5E; LCSC C21189
R523, R524, R527, R528: 100; R_0603_1608Metric; Rating 1% 100ppm/K 0603 100mW; MPN 0603WAF1000T5E; LCSC C22775
R525, R526, R529, R530: 2.2k; R_0603_1608Metric; Rating 1% 100ppm/K 0603 100mW; MPN 0603WAF2201T5E; LCSC C4190
R532, R535, R538: 20k; R_0603_1608Metric; Rating 1% 100ppm/K 0603 100mW; MPN 0603WAF2002T5E; LCSC C4184
R540, R541, R542, R543, R544: 0; R_1206_3216Metric; Rating 1206 zero-ohm link 2A rated 10A overload; MPN 1206W4F0000T5E; LCSC C17888
TP522, TP523, TP525, TP526, TP527, TP528, TP529, TP530, TP531, TP532: TestPoint; TestPoint_Pad_D1.0mm_Tight; Rating pad 1.5mm; LCSC none
U520: SN74LVC1G17; SOT-353_SC-70-5; Rating 6.5 V absolute maximum VCC, Schmitt buf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; MPN SN74LVC1G17DCKR; LCSC C10425

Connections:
/BREW_AN: C523.1, R536.2, TP529.1 (1_1); also elsewhere on the board
/BREW_SCL: D527.3 (COM), R527.2, R529.1; also elsewhere on the board
/BREW_SDA: D528.3 (COM), R528.2, R530.1, TP525.1 (1_1); also elsewhere on the board
/FLOW_IN: R522.2, U520.4; also elsewhere on the board
/Flow, pressure and spare analogue inputs/BREWA_3V3: J524.2, R543.2
/Flow, pressure and spare analogue inputs/BREWA_3V3_SRC: F523.2, R543.1, TP530.1 (1_1)
/Flow, pressure and spare analogue inputs/BREWA_DIV: R534.2, R535.1, R536.1
/Flow, pressure and spare analogue inputs/BREWA_RAW: D530.1 (A1), J524.4, R534.1
/Flow, pressure and spare analogue inputs/BREW_SCL_X: D525.1 (A1), J522.3, R527.1
/Flow, pressure and spare analogue inputs/BREW_SDA_X: D526.1 (A1), J522.4, R528.1
/Flow, pressure and spare analogue inputs/BRWD_3V3: J522.1, R541.2
/Flow, pressure and spare analogue inputs/BRWD_3V3_SRC: F521.2, R541.1, TP526.1 (1_1)
/Flow, pressure and spare analogue inputs/FLOW_F: C520.1, R521.2, R522.1, U520.2
/Flow, pressure and spare analogue inputs/FLOW_RAW: D520.1 (A1), J520.3, R520.1, R521.1
/Flow, pressure and spare analogue inputs/SPAN2_3V3: J525.2, R544.2
/Flow, pressure and spare analogue inputs/SPAN2_3V3_SRC: F524.2, R544.1, TP532.1 (1_1)
/Flow, pressure and spare analogue inputs/SPAN2_DIV: R537.2, R538.1, R539.1
/Flow, pressure and spare analogue inputs/SPAN2_RAW: D531.1 (A1), J525.4, R537.1
/Flow, pressure and spare analogue inputs/SPAREA_3V3: J523.2, R542.2
/Flow, pressure and spare analogue inputs/SPAREA_3V3_SRC: F522.2, R542.1, TP528.1 (1_1)
/Flow, pressure and spare analogue inputs/SPAREA_DIV: R531.2, R532.1, R533.1
/Flow, pressure and spare analogue inputs/SPAREA_RAW: D529.1 (A1), J523.4, R531.1
/Flow, pressure and spare analogue inputs/STMD_3V3: J521.1, R540.2
/Flow, pressure and spare analogue inputs/STMD_3V3_SRC: F520.2, R540.1, TP523.1 (1_1)
/Flow, pressure and spare analogue inputs/STM_SCL_X: D521.1 (A1), J521.3, R523.1
/Flow, pressure and spare analogue inputs/STM_SDA_X: D522.1 (A1), J521.4, R524.1
/SPARE_AN2: C524.1, R539.2, TP531.1 (1_1); also elsewhere on the board
/STMP_AN: C522.1, R533.2, TP527.1 (1_1); also elsewhere on the board
/STM_SCL: D523.3 (COM), R523.2, R525.1; also elsewhere on the board
/STM_SDA: D524.3 (COM), R524.2, R526.1, TP522.1 (1_1); also elsewhere on the board
GND: C520.2, C521.2, C522.2, C523.2, C524.2, D520.2 (A2), D521.2 (A2), D522.2 (A2), D523.1 (A), D524.1 (A), D525.2 (A2), D526.2 (A2), D527.1 (A), D528.1 (A), D529.2 (A2), D530.2 (A2), D531.2 (A2), J520.2, J521.2, J522.2, J523.3, J524.3, J525.3, R532.2, R535.2, R538.2, U520.3 (GND); also elsewhere on the board
